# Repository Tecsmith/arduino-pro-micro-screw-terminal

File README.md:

# Screw terminal board for Pro-Micro boards

| Board | URL |
|---|---|
| [Pro Micro Screw Terminal Breakout](https://tecsmith.github.io/arduino-pro-micro-screw-terminal/) |  [`c1k.it/pro1`](http://c1k.it/pro1) |

## Help, About, *etc.*

Refer to the [docs folder](docs/index.md).

<p align="center" style="color:#069">★</p>

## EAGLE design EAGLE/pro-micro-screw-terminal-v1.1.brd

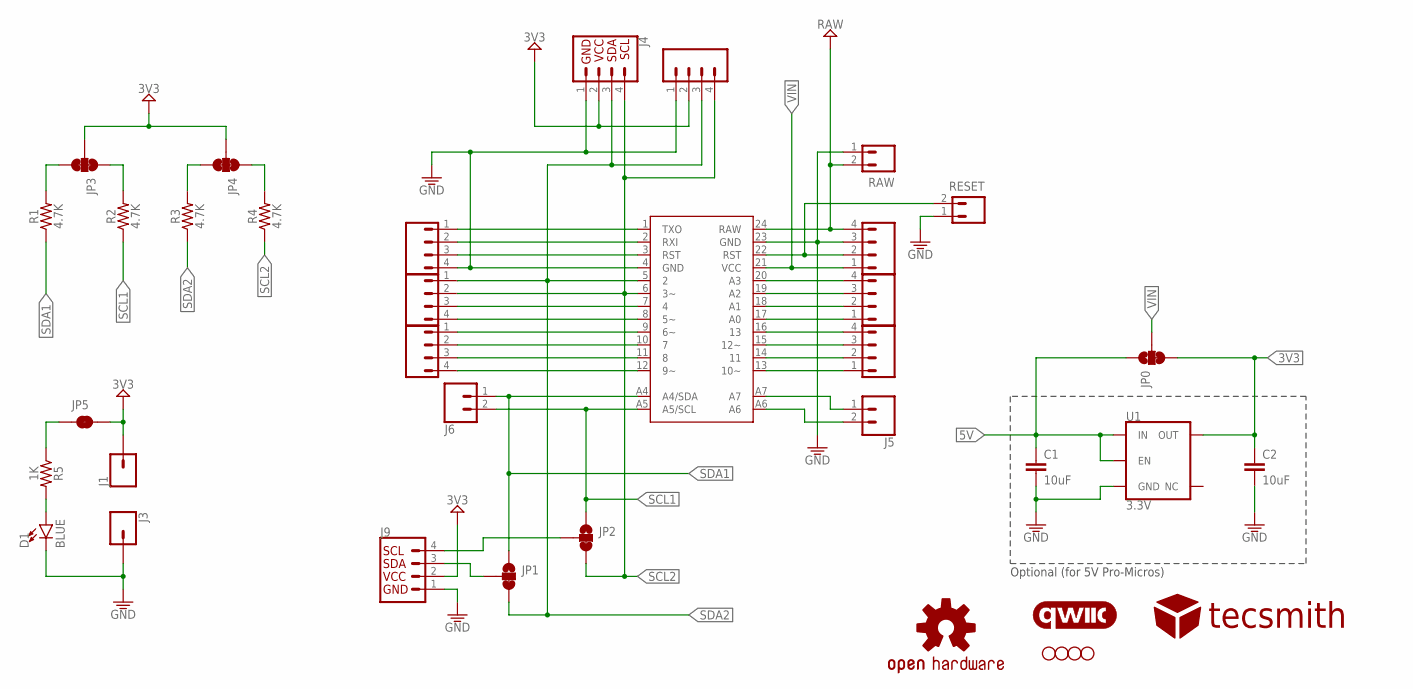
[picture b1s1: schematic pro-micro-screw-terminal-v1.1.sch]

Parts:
B1: ARDUINO_PRO_MININO_FTDI; ARDUINO_PRO_MINI
C1, C2: 10uF; 0603
D1: BLUE; LED-0603
H1, H2, H5, H6: STAND-OFF
J1, J3: CONN_01PTH_NO_SILK_YES_STOP; 1X01_NO_SILK
J2: CONN_04PTH; 1X04
J4, J9: QWIIC_RIGHT_ANGLE; JST04_1MM_RA
J5, J6: CONN_02; 1X02
JP0, JP1, JP2: JUMPER-SMT_3_1-NC_TRACE_SILK; SMT-JUMPER_3_1-NC_TRACE_SILK
JP3, JP4: JUMPER-SMT_3_2-NC_TRACE_SILK; SMT-JUMPER_3_2-NC_TRACE_SILK
JP5: JUMPER-SMT_2_NC_TRACE_SILK; SMT-JUMPER_2_NC_TRACE_SILK
LOGO1: OSHW-LOGOS; OSHW-LOGO-S
LOGO2: QWIIC_LOGO_6MM; QWIIC_6MM
R1, R2, R3, R4: 4.7K; 0805
R5: 1K; 0603
RAW: CON_02SCREW; WURTH_2431_3.5MM_2X_SCREW
RESET: JST-PH-2NS; JST-PH2-NO-SILK
U1: 3.3V; SOT23-5
U$1, U$2, U$3, U$4, U$5, U$6: CON_04SCREW; WURTH_2431_3.5MM_4X_SCREW
U$9: TECSMITH-LOGO

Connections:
3V3: C2.1, J1.1, J2.2, J4.2, J9.2, JP0.3, JP3.2, JP4.2, JP5.2, U1.5 (OUT)
5V: C1.1, JP0.1, U1.1 (IN), U1.3 (EN)
GND: B1.4 (GND), B1.23 (GND), C1.2, C2.2, D1.C, J2.1, J3.1, J4.1, J9.1, RAW.1, RESET.1, U1.2 (GND), U$1.4, U$6.3
unnamed: B1.1 (TXO), U$1.1
unnamed: B1.2 (RXI), U$1.2
unnamed: B1.3 (RST), U$1.3
unnamed: B1.A7, J5.1
unnamed: B1.A6, J5.2
unnamed: D1.A, R5.2
unnamed: B1.7 (4), U$2.3
unnamed: B1.8 (5~), U$2.4
unnamed: B1.9 (6~), U$3.1
unnamed: B1.10 (7), U$3.2
unnamed: B1.11 (8), U$3.3
unnamed: B1.12 (9~), U$3.4
unnamed: JP5.1, R5.1
unnamed: B1.22 (RST), RESET.2, U$6.2
unnamed: JP3.1, R2.2
unnamed: B1.20 (A3), U$5.4
unnamed: B1.19 (A2), U$5.3
unnamed: B1.18 (A1), U$5.2
unnamed: B1.17 (A0), U$5.1
unnamed: B1.16 (13), U$4.4
unnamed: B1.15 (12~), U$4.3
unnamed: B1.14 (11), U$4.2
unnamed: B1.13 (10~), U$4.1
unnamed: JP3.3, R1.2
unnamed: JP4.3, R3.2
unnamed: JP4.1, R4.2
RAW: B1.24 (RAW), RAW.2, U$6.4
SCL: J9.4, JP2.2
SCL1: B1.A5 (A5/SCL), J6.2, JP2.1, R2.1
SCL2: B1.6 (3~), J2.4, J4.4, JP2.3, R4.1, U$2.2
SDA: J9.3, JP1.2
SDA1: B1.A4 (A4/SDA), J6.1, JP1.1, R1.1
SDA2: B1.5 (2), J2.3, J4.3, JP1.3, R3.1, U$2.1
VIN: B1.21 (VCC), JP0.2, U$6.1

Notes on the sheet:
Optional (for 5V Pro-Micros)

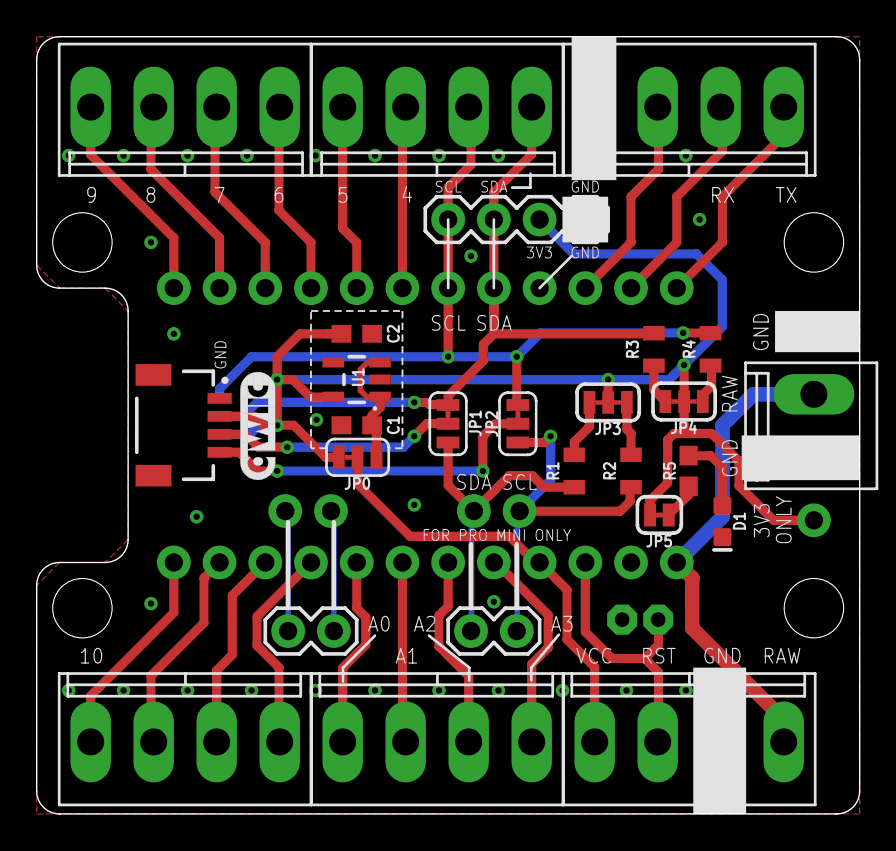
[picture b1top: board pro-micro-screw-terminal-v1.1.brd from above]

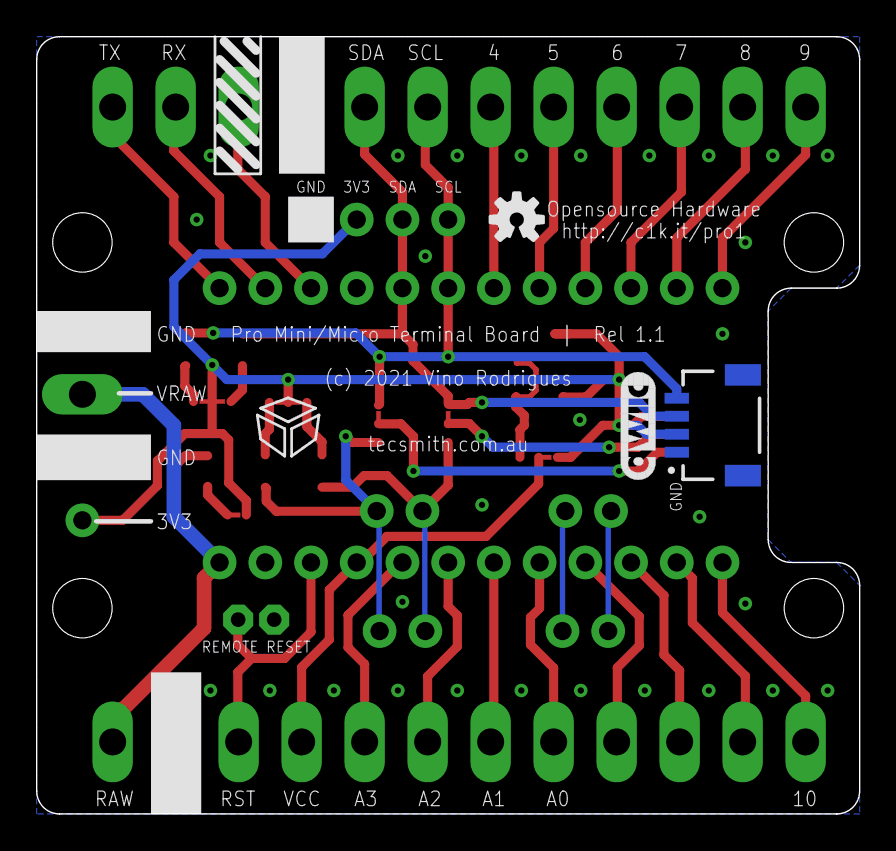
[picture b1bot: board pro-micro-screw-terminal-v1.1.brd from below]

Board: 2 copper layers, 45.7 x 43.2 mm, 39 parts (4 on the bottom side), 37 nets.

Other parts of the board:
LOGO3: QWIIC_LOGO_6MM; QWIIC_6MM

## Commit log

2021-07-04 moved from fan-control project
2021-07-05 move items from arduino-fan-control-v2 project
2021-09-22 v1.1 add a V/Reg to account for the new Qwiic Pro Micro USB-C that uses a 5v VCC, but a 3v3 qwiic bus

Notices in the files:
EAGLE/pro-micro-screw-terminal-v1.1.brd:
(c) 2021 Vino Rodrigues
parts and their libraries:
SparkFun-Connectors: Licensing: Creative Commons ShareAlike 4.0 International - https://creativecommons.org/licenses/by-sa/4.0
